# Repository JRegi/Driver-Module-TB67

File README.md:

# Dual Driver Module with TB67H450FNG

## **Description**
A little module with two TB67H450FNG full-bridge drivers, designed to be small while maintaining a decent thermal performance.

## **Repository content**

- */DIY-Module_TB67H450FNG* - Intended for homemade PCB fabrication.
- */PCBWay-Module_TB67H450FNG* - Intended for PCBWay Quick-Turn PCB capabilities.

# 3D view

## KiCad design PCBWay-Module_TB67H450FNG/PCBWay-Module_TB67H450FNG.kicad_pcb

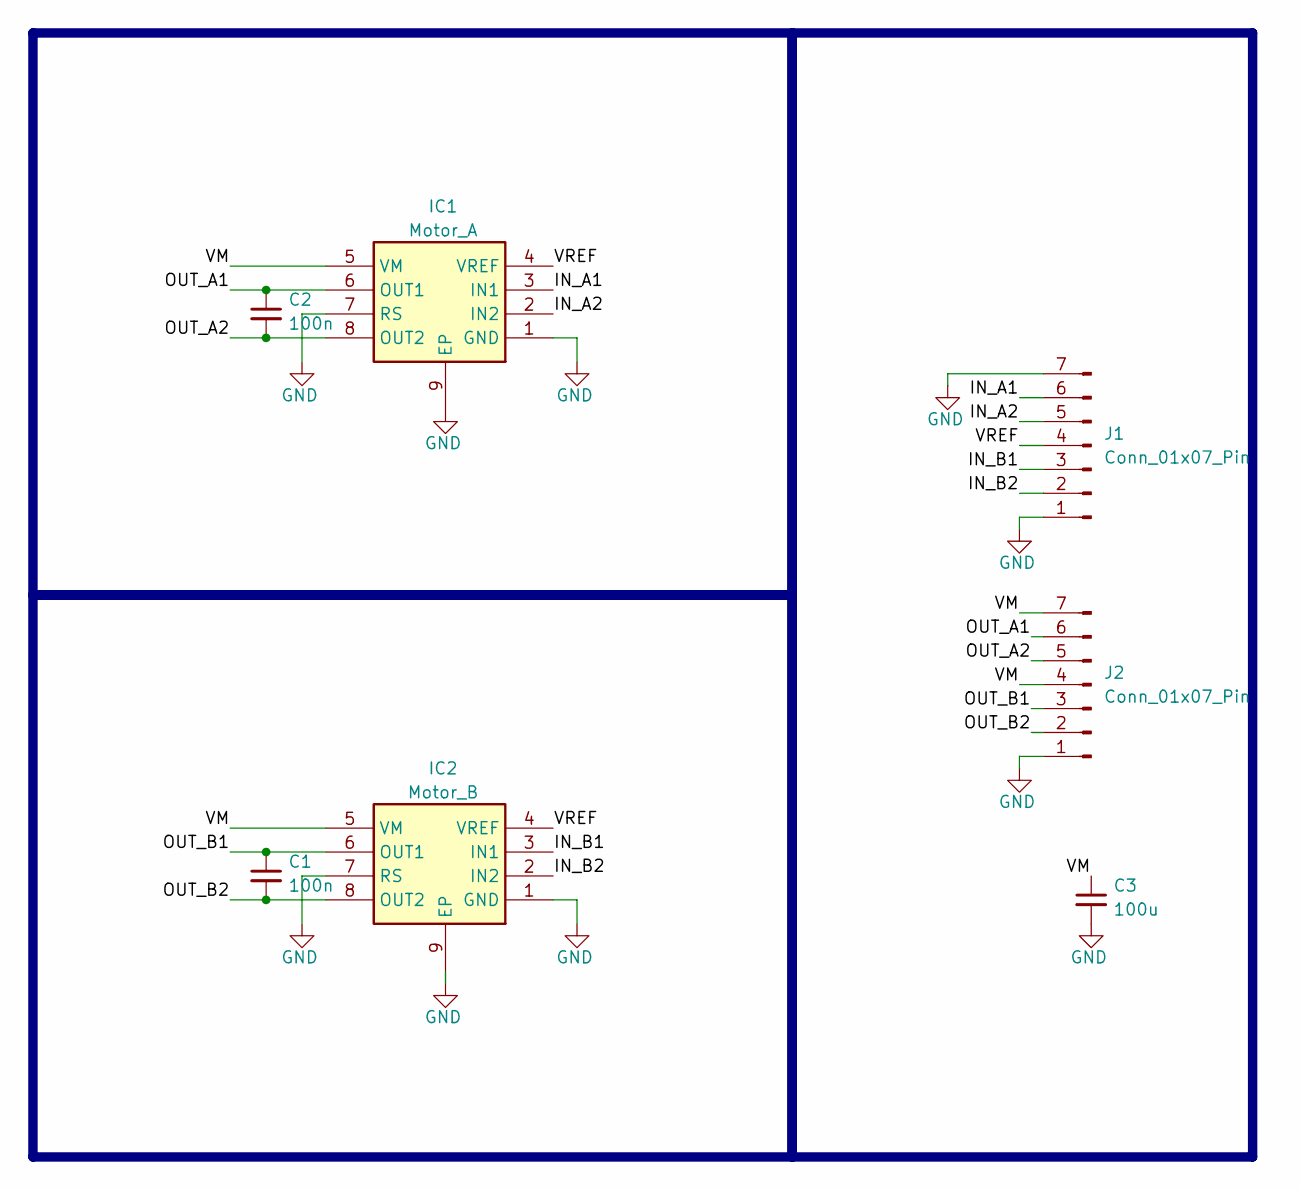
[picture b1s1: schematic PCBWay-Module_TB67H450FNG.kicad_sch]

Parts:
C1, C2: 100n; C_0805_2012Metric
C3: 100u; C_Disc_D4.3mm_W1.9mm_P5.00mm
IC1: Motor_A; TB67H450FNG_EL; Mouser Part Number 757-TB67H450FNGEL
IC2: Motor_B; TB67H450FNG_EL; Mouser Part Number 757-TB67H450FNGEL
J1, J2: Conn_01x07_Pin; PinHeader_1x07_P2.54mm_Vertical

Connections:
/IN_A1: IC1.3 (IN1), J1.6
/IN_A2: IC1.2 (IN2), J1.5
/IN_B1: IC2.3 (IN1), J1.3
/IN_B2: IC2.2 (IN2), J1.2
/OUT_A1: C2.1, IC1.6 (OUT1), J2.6
/OUT_A2: C2.2, IC1.8 (OUT2), J2.5
/OUT_B1: C1.1, IC2.6 (OUT1), J2.3
/OUT_B2: C1.2, IC2.8 (OUT2), J2.2
/VM: C3.1, IC1.5 (VM), IC2.5 (VM), J2.4, J2.7
/VREF: IC1.4 (VREF), IC2.4 (VREF), J1.4
GND: C3.2, IC1.1 (GND), IC1.7 (RS), IC1.9 (EP), IC2.1 (GND), IC2.7 (RS), IC2.9 (EP), J1.1, J1.7, J2.1

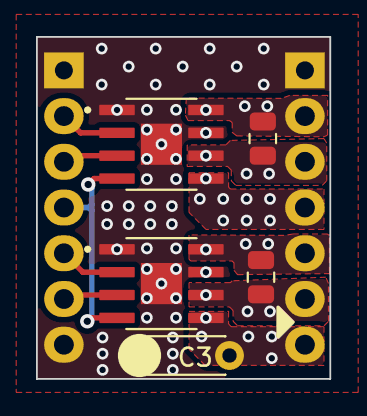
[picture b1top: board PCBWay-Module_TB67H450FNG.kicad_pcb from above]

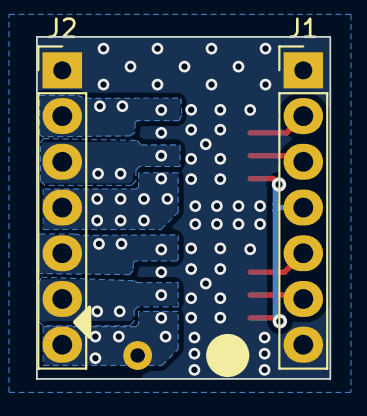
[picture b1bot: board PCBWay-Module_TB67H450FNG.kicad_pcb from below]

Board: 2 copper layers, 16.3 x 19.0 mm, 7 parts (2 on the bottom side), 11 nets.

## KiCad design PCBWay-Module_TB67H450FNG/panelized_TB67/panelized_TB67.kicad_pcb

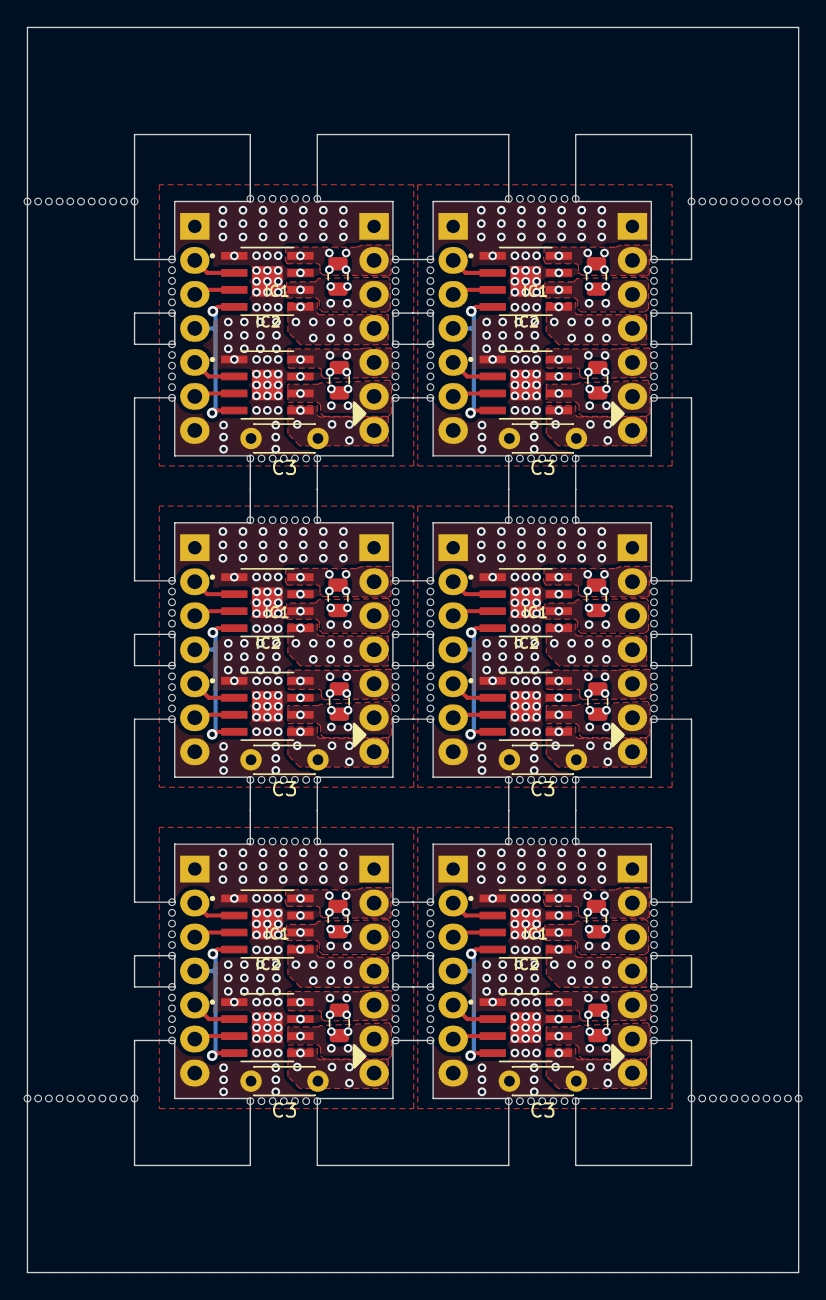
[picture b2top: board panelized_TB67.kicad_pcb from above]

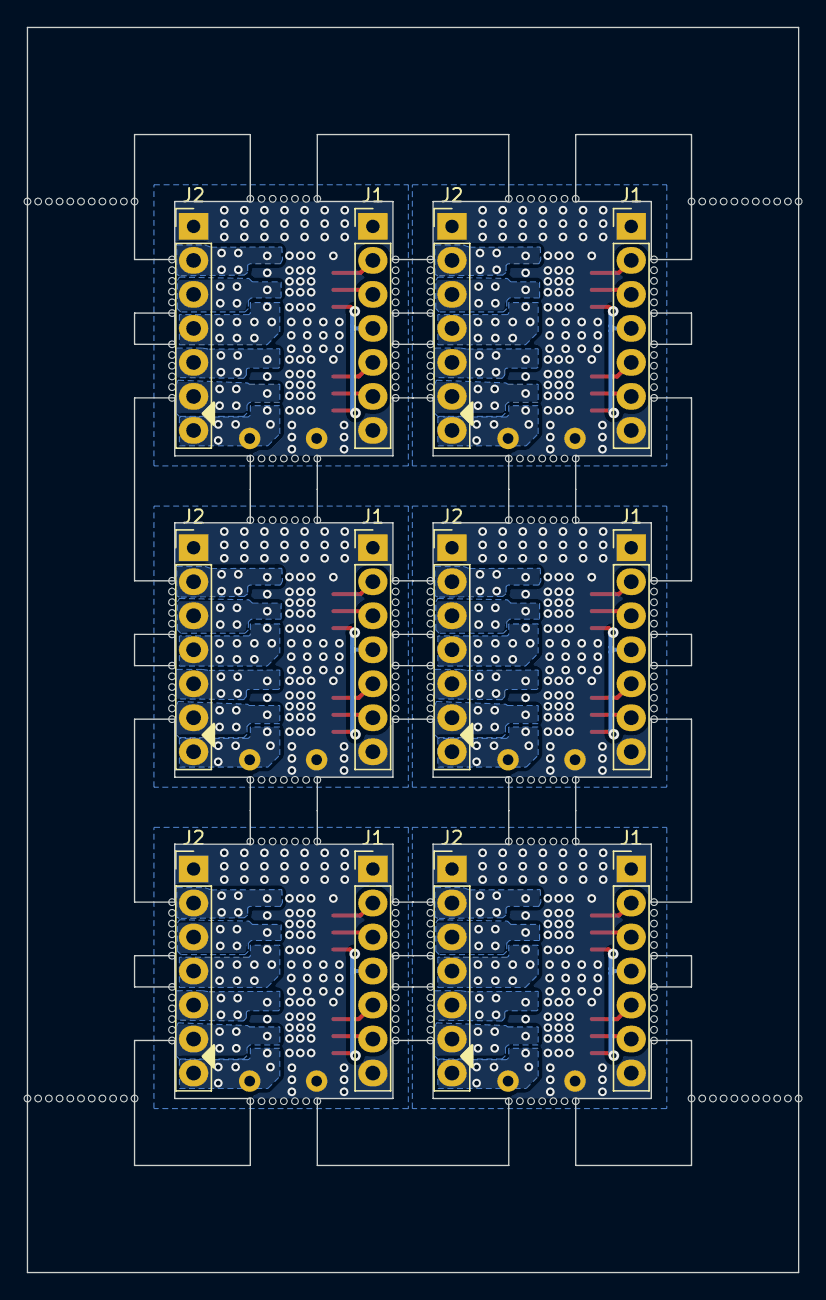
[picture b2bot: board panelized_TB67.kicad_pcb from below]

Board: 2 copper layers, 57.6 x 93.0 mm, 314 parts (12 on the bottom side), 66 nets.

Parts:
C1, C1#2, C1#3, C1#4, C1#5, C1#6, C2, C2#2, C2#3, C2#4, C2#5, C2#6: 100; C_0805_2012Metric
C3, C3#2, C3#3, C3#4, C3#5, C3#6: 100; C_Disc_D4.3mm_W1.9mm_P5.00mm
IC1, IC1#2, IC1#3, IC1#4, IC1#5, IC1#6: Motor_A; TB67H450FNG_EL
IC2, IC2#2, IC2#3, IC2#4, IC2#5, IC2#6: Motor_B; TB67H450FNG_EL
J1, J1#2, J1#3, J1#4, J1#5, J1#6, J2, J2#2, J2#3, J2#4, J2#5, J2#6: Conn_01x07_Pin; PinHeader_1x07_P2.54mm_Vertical
KiKit_MB_1_1, KiKit_MB_1_2, KiKit_MB_1_3, KiKit_MB_1_4, KiKit_MB_1_5, KiKit_MB_1_6, KiKit_MB_2_1, KiKit_MB_2_2, KiKit_MB_2_3, KiKit_MB_2_4, KiKit_MB_2_5, KiKit_MB_2_6, KiKit_MB_3_1, KiKit_MB_3_2, KiKit_MB_3_3, KiKit_MB_3_4, KiKit_MB_3_5, KiKit_MB_3_6, KiKit_MB_4_1, KiKit_MB_4_2, KiKit_MB_4_3, KiKit_MB_4_4, KiKit_MB_4_5, KiKit_MB_4_6, KiKit_MB_5_1, KiKit_MB_5_2, KiKit_MB_5_3, KiKit_MB_5_4, KiKit_MB_5_5, KiKit_MB_5_6, KiKit_MB_5_7, KiKit_MB_6_1, KiKit_MB_6_2, KiKit_MB_6_3, KiKit_MB_6_4, KiKit_MB_6_5, KiKit_MB_6_6, KiKit_MB_6_7, KiKit_MB_7_1, KiKit_MB_7_2, KiKit_MB_7_3, KiKit_MB_7_4, KiKit_MB_7_5, KiKit_MB_7_6, KiKit_MB_8_1, KiKit_MB_8_2, KiKit_MB_8_3, KiKit_MB_8_4, KiKit_MB_8_5, KiKit_MB_8_6, KiKit_MB_9_1, KiKit_MB_9_2, KiKit_MB_9_3, KiKit_MB_9_4, KiKit_MB_9_5, KiKit_MB_9_6, KiKit_MB_10_1, KiKit_MB_10_2, KiKit_MB_10_3, KiKit_MB_10_4, KiKit_MB_10_5, KiKit_MB_10_6, KiKit_MB_11_1, KiKit_MB_11_2, KiKit_MB_11_3, KiKit_MB_11_4, KiKit_MB_11_5, KiKit_MB_11_6, KiKit_MB_11_7, KiKit_MB_12_1, KiKit_MB_12_2, KiKit_MB_12_3, KiKit_MB_12_4, KiKit_MB_12_5, KiKit_MB_12_6, KiKit_MB_12_7, KiKit_MB_13_1, KiKit_MB_13_2, KiKit_MB_13_3, KiKit_MB_13_4, KiKit_MB_13_5, KiKit_MB_13_6, KiKit_MB_14_1, KiKit_MB_14_2, KiKit_MB_14_3, KiKit_MB_14_4, KiKit_MB_14_5, KiKit_MB_14_6, KiKit_MB_15_1, KiKit_MB_15_2, KiKit_MB_15_3, KiKit_MB_15_4, KiKit_MB_15_5, KiKit_MB_15_6, KiKit_MB_16_1, KiKit_MB_16_2, KiKit_MB_16_3, KiKit_MB_16_4, KiKit_MB_16_5, KiKit_MB_16_6, KiKit_MB_17_1, KiKit_MB_17_2, KiKit_MB_17_3, KiKit_MB_17_4, KiKit_MB_17_5, KiKit_MB_17_6, KiKit_MB_17_7, KiKit_MB_18_1, KiKit_MB_18_2, KiKit_MB_18_3, KiKit_MB_18_4, KiKit_MB_18_5, KiKit_MB_18_6, KiKit_MB_18_7, KiKit_MB_19_1, KiKit_MB_19_2, KiKit_MB_19_3, KiKit_MB_19_4, KiKit_MB_19_5, KiKit_MB_19_6, KiKit_MB_20_1, KiKit_MB_20_2, KiKit_MB_20_3, KiKit_MB_20_4, KiKit_MB_20_5, KiKit_MB_20_6, KiKit_MB_21_1, KiKit_MB_21_2, KiKit_MB_21_3, KiKit_MB_21_4, KiKit_MB_21_5, KiKit_MB_21_6, KiKit_MB_22_1, KiKit_MB_22_2, KiKit_MB_22_3, KiKit_MB_22_4, KiKit_MB_22_5, KiKit_MB_22_6, KiKit_MB_23_1, KiKit_MB_23_2, KiKit_MB_23_3, KiKit_MB_23_4, KiKit_MB_23_5, KiKit_MB_23_6, KiKit_MB_23_7, KiKit_MB_24_1, KiKit_MB_24_2, KiKit_MB_24_3, KiKit_MB_24_4, KiKit_MB_24_5, KiKit_MB_24_6, KiKit_MB_24_7, KiKit_MB_25_1, KiKit_MB_25_2, KiKit_MB_25_3, KiKit_MB_25_4, KiKit_MB_25_5, KiKit_MB_25_6, KiKit_MB_26_1, KiKit_MB_26_2, KiKit_MB_26_3, KiKit_MB_26_4, KiKit_MB_26_5, KiKit_MB_26_6, KiKit_MB_27_1, KiKit_MB_27_2, KiKit_MB_27_3, KiKit_MB_27_4, KiKit_MB_27_5, KiKit_MB_27_6, KiKit_MB_28_1, KiKit_MB_28_2, KiKit_MB_28_3, KiKit_MB_28_4, KiKit_MB_28_5, KiKit_MB_28_6, KiKit_MB_29_1, KiKit_MB_29_2, KiKit_MB_29_3, KiKit_MB_29_4, KiKit_MB_29_5, KiKit_MB_29_6, KiKit_MB_29_7, KiKit_MB_30_1, KiKit_MB_30_2, KiKit_MB_30_3, KiKit_MB_30_4, KiKit_MB_30_5, KiKit_MB_30_6, KiKit_MB_30_7, KiKit_MB_31_1, KiKit_MB_31_2, KiKit_MB_31_3, KiKit_MB_31_4, KiKit_MB_31_5, KiKit_MB_31_6, KiKit_MB_32_1, KiKit_MB_32_2, KiKit_MB_32_3, KiKit_MB_32_4, KiKit_MB_32_5, KiKit_MB_32_6, KiKit_MB_33_1, KiKit_MB_33_2, KiKit_MB_33_3, KiKit_MB_33_4, KiKit_MB_33_5, KiKit_MB_33_6, KiKit_MB_34_1, KiKit_MB_34_2, KiKit_MB_34_3, KiKit_MB_34_4, KiKit_MB_34_5, KiKit_MB_34_6, KiKit_MB_35_1, KiKit_MB_35_2, KiKit_MB_35_3, KiKit_MB_35_4, KiKit_MB_35_5, KiKit_MB_35_6, KiKit_MB_35_7, KiKit_MB_36_1, KiKit_MB_36_2, KiKit_MB_36_3, KiKit_MB_36_4, KiKit_MB_36_5, KiKit_MB_36_6, KiKit_MB_36_7, KiKit_MB_37_1, KiKit_MB_37_2, KiKit_MB_37_3, KiKit_MB_37_4, KiKit_MB_37_5, KiKit_MB_37_6, KiKit_MB_37_7, KiKit_MB_37_8, KiKit_MB_37_9, KiKit_MB_37_10, KiKit_MB_37_11, KiKit_MB_38_1, KiKit_MB_38_2, KiKit_MB_38_3, KiKit_MB_38_4, KiKit_MB_38_5, KiKit_MB_38_6, KiKit_MB_38_7, KiKit_MB_38_8, KiKit_MB_38_9, KiKit_MB_38_10, KiKit_MB_38_11, KiKit_MB_39_1, KiKit_MB_39_2, KiKit_MB_39_3, KiKit_MB_39_4, KiKit_MB_39_5, KiKit_MB_39_6, KiKit_MB_39_7, KiKit_MB_39_8, KiKit_MB_39_9, KiKit_MB_39_10, KiKit_MB_39_11, KiKit_MB_40_1, KiKit_MB_40_2, KiKit_MB_40_3, KiKit_MB_40_4, KiKit_MB_40_5, KiKit_MB_40_6, KiKit_MB_40_7, KiKit_MB_40_8, KiKit_MB_40_9, KiKit_MB_40_10, KiKit_MB_40_11: NPTH

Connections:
Board_0-/IN_A1: C2#3.1, IC1#3.3 (IN1), J1#4.6
Board_0-/IN_A2: C2#3.2, IC1#3.2 (IN2), J1#4.5
Board_0-/IN_B1: C1#6.1, IC2#3.3 (IN1), J1#4.3
Board_0-/IN_B2: C1#6.2, IC2#3.2 (IN2), J1#4.2
Board_0-/OUT_A1: IC1#3.6 (OUT1), J2#5.6
Board_0-/OUT_A2: IC1#3.8 (OUT2), J2#5.5
Board_0-/OUT_B1: IC2#3.6 (OUT1), J2#5.3
Board_0-/OUT_B2: IC2#3.8 (OUT2), J2#5.2
Board_0-/VM: C3#4.1, IC1#3.5 (VM), IC2#3.5 (VM), J2#5.4, J2#5.7
Board_0-/VREF: IC1#3.4 (VREF), IC2#3.4 (VREF), J1#4.4
Board_0-GND: C3#4.2, IC1#3.1 (GND), IC1#3.7 (RS), IC1#3.9 (EP), IC2#3.1 (GND), IC2#3.7 (RS), IC2#3.9 (EP), J1#4.1, J1#4.7, J2#5.1
Board_1-/IN_A1: C2#4.1, IC1#5.3 (IN1), J1#5.6
Board_1-/IN_A2: C2#4.2, IC1#5.2 (IN2), J1#5.5
Board_1-/IN_B1: C1#5.1, IC2.3 (IN1), J1#5.3
Board_1-/IN_B2: C1#5.2, IC2.2 (IN2), J1#5.2
Board_1-/OUT_A1: IC1#5.6 (OUT1), J2#4.6
Board_1-/OUT_A2: IC1#5.8 (OUT2), J2#4.5
Board_1-/OUT_B1: IC2.6 (OUT1), J2#4.3
Board_1-/OUT_B2: IC2.8 (OUT2), J2#4.2
Board_1-/VM: C3#5.1, IC1#5.5 (VM), IC2.5 (VM), J2#4.4, J2#4.7
Board_1-/VREF: IC1#5.4 (VREF), IC2.4 (VREF), J1#5.4
Board_1-GND: C3#5.2, IC1#5.1 (GND), IC1#5.7 (RS), IC1#5.9 (EP), IC2.1 (GND), IC2.7 (RS), IC2.9 (EP), J1#5.1, J1#5.7, J2#4.1
Board_2-/IN_A1: C2#5.1, IC1#6.3 (IN1), J1#6.6
Board_2-/IN_A2: C2#5.2, IC1#6.2 (IN2), J1#6.5
Board_2-/IN_B1: C1#4.1, IC2#6.3 (IN1), J1#6.3
Board_2-/IN_B2: C1#4.2, IC2#6.2 (IN2), J1#6.2
Board_2-/OUT_A1: IC1#6.6 (OUT1), J2#3.6
Board_2-/OUT_A2: IC1#6.8 (OUT2), J2#3.5
Board_2-/OUT_B1: IC2#6.6 (OUT1), J2#3.3
Board_2-/OUT_B2: IC2#6.8 (OUT2), J2#3.2
Board_2-/VM: C3#3.1, IC1#6.5 (VM), IC2#6.5 (VM), J2#3.4, J2#3.7
Board_2-/VREF: IC1#6.4 (VREF), IC2#6.4 (VREF), J1#6.4
Board_2-GND: C3#3.2, IC1#6.1 (GND), IC1#6.7 (RS), IC1#6.9 (EP), IC2#6.1 (GND), IC2#6.7 (RS), IC2#6.9 (EP), J1#6.1, J1#6.7, J2#3.1
Board_3-/IN_A1: C2.1, IC1#4.3 (IN1), J1.6
Board_3-/IN_A2: C2.2, IC1#4.2 (IN2), J1.5
Board_3-/IN_B1: C1#3.1, IC2#5.3 (IN1), J1.3
Board_3-/IN_B2: C1#3.2, IC2#5.2 (IN2), J1.2
Board_3-/OUT_A1: IC1#4.6 (OUT1), J2#6.6
Board_3-/OUT_A2: IC1#4.8 (OUT2), J2#6.5
Board_3-/OUT_B1: IC2#5.6 (OUT1), J2#6.3
Board_3-/OUT_B2: IC2#5.8 (OUT2), J2#6.2
Board_3-/VM: C3.1, IC1#4.5 (VM), IC2#5.5 (VM), J2#6.4, J2#6.7
Board_3-/VREF: IC1#4.4 (VREF), IC2#5.4 (VREF), J1.4
Board_3-GND: C3.2, IC1#4.1 (GND), IC1#4.7 (RS), IC1#4.9 (EP), IC2#5.1 (GND), IC2#5.7 (RS), IC2#5.9 (EP), J1.1, J1.7, J2#6.1
Board_4-/IN_A1: C2#2.1, IC1.3 (IN1), J1#2.6
Board_4-/IN_A2: C2#2.2, IC1.2 (IN2), J1#2.5
Board_4-/IN_B1: C1.1, IC2#4.3 (IN1), J1#2.3
Board_4-/IN_B2: C1.2, IC2#4.2 (IN2), J1#2.2
Board_4-/OUT_A1: IC1.6 (OUT1), J2#2.6
Board_4-/OUT_A2: IC1.8 (OUT2), J2#2.5
Board_4-/OUT_B1: IC2#4.6 (OUT1), J2#2.3
Board_4-/OUT_B2: IC2#4.8 (OUT2), J2#2.2
Board_4-/VM: C3#2.1, IC1.5 (VM), IC2#4.5 (VM), J2#2.4, J2#2.7
Board_4-/VREF: IC1.4 (VREF), IC2#4.4 (VREF), J1#2.4
Board_4-GND: C3#2.2, IC1.1 (GND), IC1.7 (RS), IC1.9 (EP), IC2#4.1 (GND), IC2#4.7 (RS), IC2#4.9 (EP), J1#2.1, J1#2.7, J2#2.1
Board_5-/IN_A1: C2#6.1, IC1#2.3 (IN1), J1#3.6
Board_5-/IN_A2: C2#6.2, IC1#2.2 (IN2), J1#3.5
Board_5-/IN_B1: C1#2.1, IC2#2.3 (IN1), J1#3.3
Board_5-/IN_B2: C1#2.2, IC2#2.2 (IN2), J1#3.2
Board_5-/OUT_A1: IC1#2.6 (OUT1), J2.6
Board_5-/OUT_A2: IC1#2.8 (OUT2), J2.5
Board_5-/OUT_B1: IC2#2.6 (OUT1), J2.3
Board_5-/OUT_B2: IC2#2.8 (OUT2), J2.2
Board_5-/VM: C3#6.1, IC1#2.5 (VM), IC2#2.5 (VM), J2.4, J2.7
Board_5-/VREF: IC1#2.4 (VREF), IC2#2.4 (VREF), J1#3.4
Board_5-GND: C3#6.2, IC1#2.1 (GND), IC1#2.7 (RS), IC1#2.9 (EP), IC2#2.1 (GND), IC2#2.7 (RS), IC2#2.9 (EP), J1#3.1, J1#3.7, J2.1

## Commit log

2024-09-08 KiCad projects.
2024-09-08 Removed capacitors & update README.md
2024-09-08 Generated gerber files
2024-09-08 Updated orientation indicator
2024-09-09 Backup
2024-09-09 Fixed vias
2024-09-15 Added capacitors
2024-09-15 Modified capacitors value
2024-09-16 gerbers
2024-09-16 panels
2024-09-16 panels again
2024-09-19 fixed capacitor footprint & regenerated gerbers
